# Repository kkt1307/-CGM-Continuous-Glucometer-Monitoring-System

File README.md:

# Indigenous Continuous Glucose Monitoring (CGM) System

**Electrochemical Sensor Interface | Custom Analog Front End | PCB Design | ESP32 | IoT**

## Overview

This project focuses on the development of an indigenous Continuous Glucose Monitoring (CGM) prototype using an electrochemical sensing interface, a custom Analog Front End (AFE), and an ESP32-based embedded acquisition system.

The work involved studying and reverse-engineering a commercial CGM sensor interface, developing custom signal-conditioning circuitry, designing PCBs, acquiring low-level electrochemical sensor signals, and implementing remote data logging using Firebase.

The primary engineering focus was on analog signal acquisition, sensor interfacing, hardware development, and embedded data processing.

## System Architecture

The system follows this signal acquisition pipeline:

1. Electrochemical glucose sensor
2. Custom potentiostat and Transimpedance Amplifier (TIA)
3. Analog-to-Digital Conversion
4. ESP32-based data acquisition
5. Python communication bridge
6. Firebase Realtime Database

## Technical Contributions

### 1. Electrochemical Sensor Interface
- Studied the working principle of electrochemical glucose sensors.
- Investigated the three-electrode sensing architecture: Working Electrode (WE), Reference Electrode (RE), and Counter Electrode (CE).
- Reverse-engineered the interface of a commercial CGM sensor.
- Investigated sensor current characteristics and electrical response.

### 2. Custom Analog Front End (AFE)
- Designed a custom analog front end for electrochemical signal acquisition.
- Developed Transimpedance Amplifier (TIA) circuits for converting low-level sensor currents into measurable voltages.
- Worked on virtual ground generation and precision voltage referencing.
- Investigated gain selection, signal conditioning, and analog stability.
- Simulated circuit behavior using LTSpice.

### 3. PCB Design and Hardware Development
- Designed circuit schematics and PCB layouts using KiCad.
- Integrated analog signal-conditioning stages, ADC interfacing, voltage regulation, and sensor connectors.
- Worked on grounding, power distribution, and analog signal routing.
- Prepared BOMs and Gerber manufacturing files.
- Evaluated PCB fabrication and assembly requirements.

### 4. Embedded Systems and Data Acquisition
- Developed ESP32 firmware for sensor data acquisition.
- Implemented ADC sampling and voltage conversion.
- Processed sensor measurements using filtering techniques.
- Calculated sensor current from the measured TIA output and feedback resistance.
- Implemented serial communication for transferring measurement data.

### 5. IoT and Remote Data Monitoring
- Developed a Python-based communication bridge.
- Integrated sensor measurements with Firebase Realtime Database.
- Implemented real-time logging of ADC values, TIA voltage, sensor current, and device status.

## Hardware Components

| Component | Application |
|---|---|
| ESP32 | Embedded controller |
| Operational Amplifiers | Custom analog front end |
| ADS1115 | External ADC |
| LM4040 | Precision voltage reference |
| AP2112K-3.3 | Voltage regulation |
| TVS / ESD Protection | Circuit protection |
| Electrochemical Sensor | Glucose sensing interface |

*Component selection may vary across prototype revisions.*

## Software and Tools

- **PCB Design:** KiCad
- **Circuit Simulation:** LTSpice
- **Embedded Development:** Arduino IDE, C/C++
- **Microcontroller:** ESP32
- **Data Processing:** Python
- **Database:** Firebase Realtime Database
- **Communication:** Serial Communication

## Experimental Results

The prototype was tested for electrical signal acquisition and sensor-current measurement.

Example measurements:

| ADC Reading | TIA Output | Sensor Current |
|---:|---:|---:|
| 111 | 89.45 mV | 4.47 µA |
| 251 | 202.27 mV | 10.11 µA |

The measurements demonstrate the acquisition and conversion of low-level sensor currents into digital readings.

Additional characterization data and measurement plots are available in the `results/` directory.

## Repository Structure

```text
├── docs/          # Project documentation
├── hardware/      # Schematics, PCB layouts and BOM
├── firmware/      # ESP32 firmware
├── software/      # Python and Firebase integration
├── simulation/    # LTSpice simulations
├── results/       # Experimental data and plots
└── images/        # Prototype and PCB photographs
```

## Current Development Status

The project covers prototype-level electronics development, analog signal acquisition, embedded firmware, and remote data logging.

Further work is required for:
- Sensor-specific glucose calibration.
- Long-term sensor stability and drift characterization.
- Temperature compensation.
- Measurement accuracy and repeatability evaluation.
- Clinical validation and safety evaluation.

**Note:** This is an electronics development prototype and is not a clinically validated glucose monitoring device. Its readings should not be used for medical decisions.

## Acknowledgements

Developed as part of research and hardware development work at the Centre for Nanotechnology, IIT Guwahati.

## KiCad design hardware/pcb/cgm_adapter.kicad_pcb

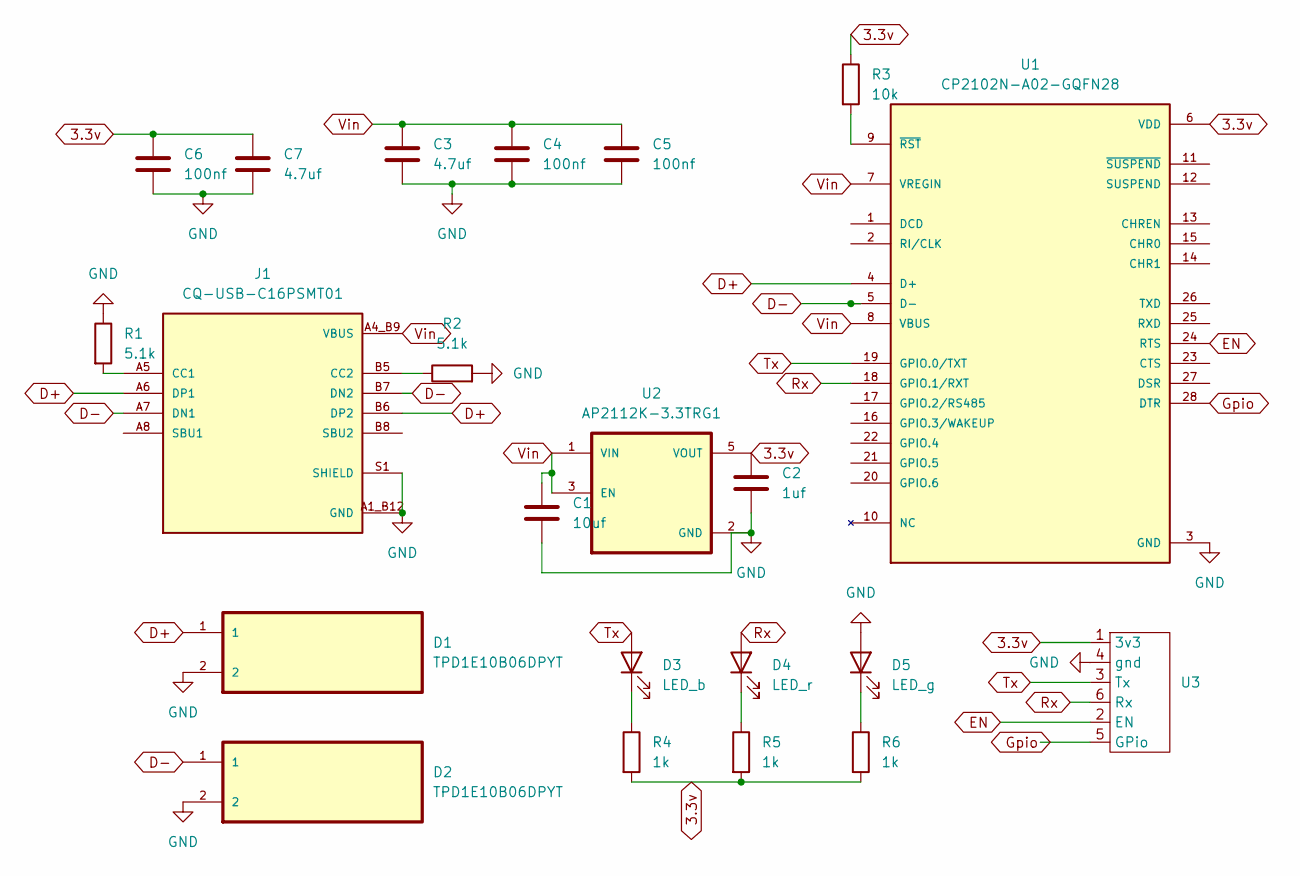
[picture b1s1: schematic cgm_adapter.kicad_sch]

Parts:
C1: 10uf; C_0201_0603Metric
C2: 1uf; C_0201_0603Metric
C3, C7: 4.7uf; C_0201_0603Metric
C4, C5, C6: 100nf; C_0201_0603Metric
D1, D2: TPD1E10B06DPYT; DIO_TPD1E05U06DPYR
D3: LED_b; LED_0603_1608Metric
D4: LED_r; LED_0603_1608Metric
D5: LED_g; LED_0603_1608Metric
J1: CQ-USB-C16PSMT01; SHENZHEN-CHUANGQIN-TECHNOLOGY_CQ-USB-C16PSMT01; PARTREV A
R1, R2: 5.1k; R_0201_0603Metric
R3: 10k; R_0201_0603Metric
R4, R5, R6: 1k; R_0201_0603Metric
U1: CP2102N-A02-GQFN28; QFN50P500X500X80-29N; PARTREV 1.5
U2: AP2112K-3.3TRG1; SOT95P285X140-5N; PARTREV 2-2
U3: 3x2_pogo_pins

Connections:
3.3v: C2.1, C6.1, C7.1, R3.1, R4.2, R5.2, R6.2, U1.6 (VDD), U2.5 (VOUT), U3.1 (3v3)
D+: D1.1, J1.A6 (DP1), J1.B6 (DP2), U1.4 (D+)
D-: D2.1, J1.A7 (DN1), J1.B7 (DN2), U1.5 (D-)
EN: U1.24 (RTS), U3.2 (EN)
GND: C1.2, C2.2, C3.2, C4.2, C5.2, C6.2, C7.2, D1.2, D2.2, D5.2 (A), J1.A1_B12 (GND), J1.B1_A12 (GND), J1.S1 (SHIELD), J1.S2 (SHIELD), J1.S3 (SHIELD), J1.S4 (SHIELD), R1.1, R2.2, U1.3 (GND), U1.29 (GND), U2.2 (GND), U3.4 (gnd)
Gpio: U1.28 (DTR), U3.5 (GPio)
unnamed: D3.1 (K), R4.1
unnamed: D4.1 (K), R5.1
unnamed: D5.1 (K), R6.1
unnamed: J1.A5 (CC1), R1.2
unnamed: J1.B5 (CC2), R2.1
unnamed: R3.2, U1.9 (~RST)
Rx: D4.2 (A), U1.18 (GPIO.1/RXT), U3.6 (Rx)
Tx: D3.2 (A), U1.19 (GPIO.0/TXT), U3.3 (Tx)
Vin: C1.1, C3.1, C4.1, C5.1, J1.A4_B9 (VBUS), J1.B4_A9 (VBUS), U1.7 (VREGIN), U1.8 (VBUS), U2.1 (VIN), U2.3 (EN)

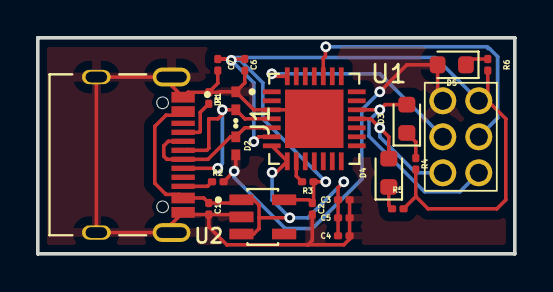
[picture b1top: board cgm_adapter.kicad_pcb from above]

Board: 2 copper layers, 26.5 x 12.0 mm, 22 parts (0 on the bottom side), 15 nets.

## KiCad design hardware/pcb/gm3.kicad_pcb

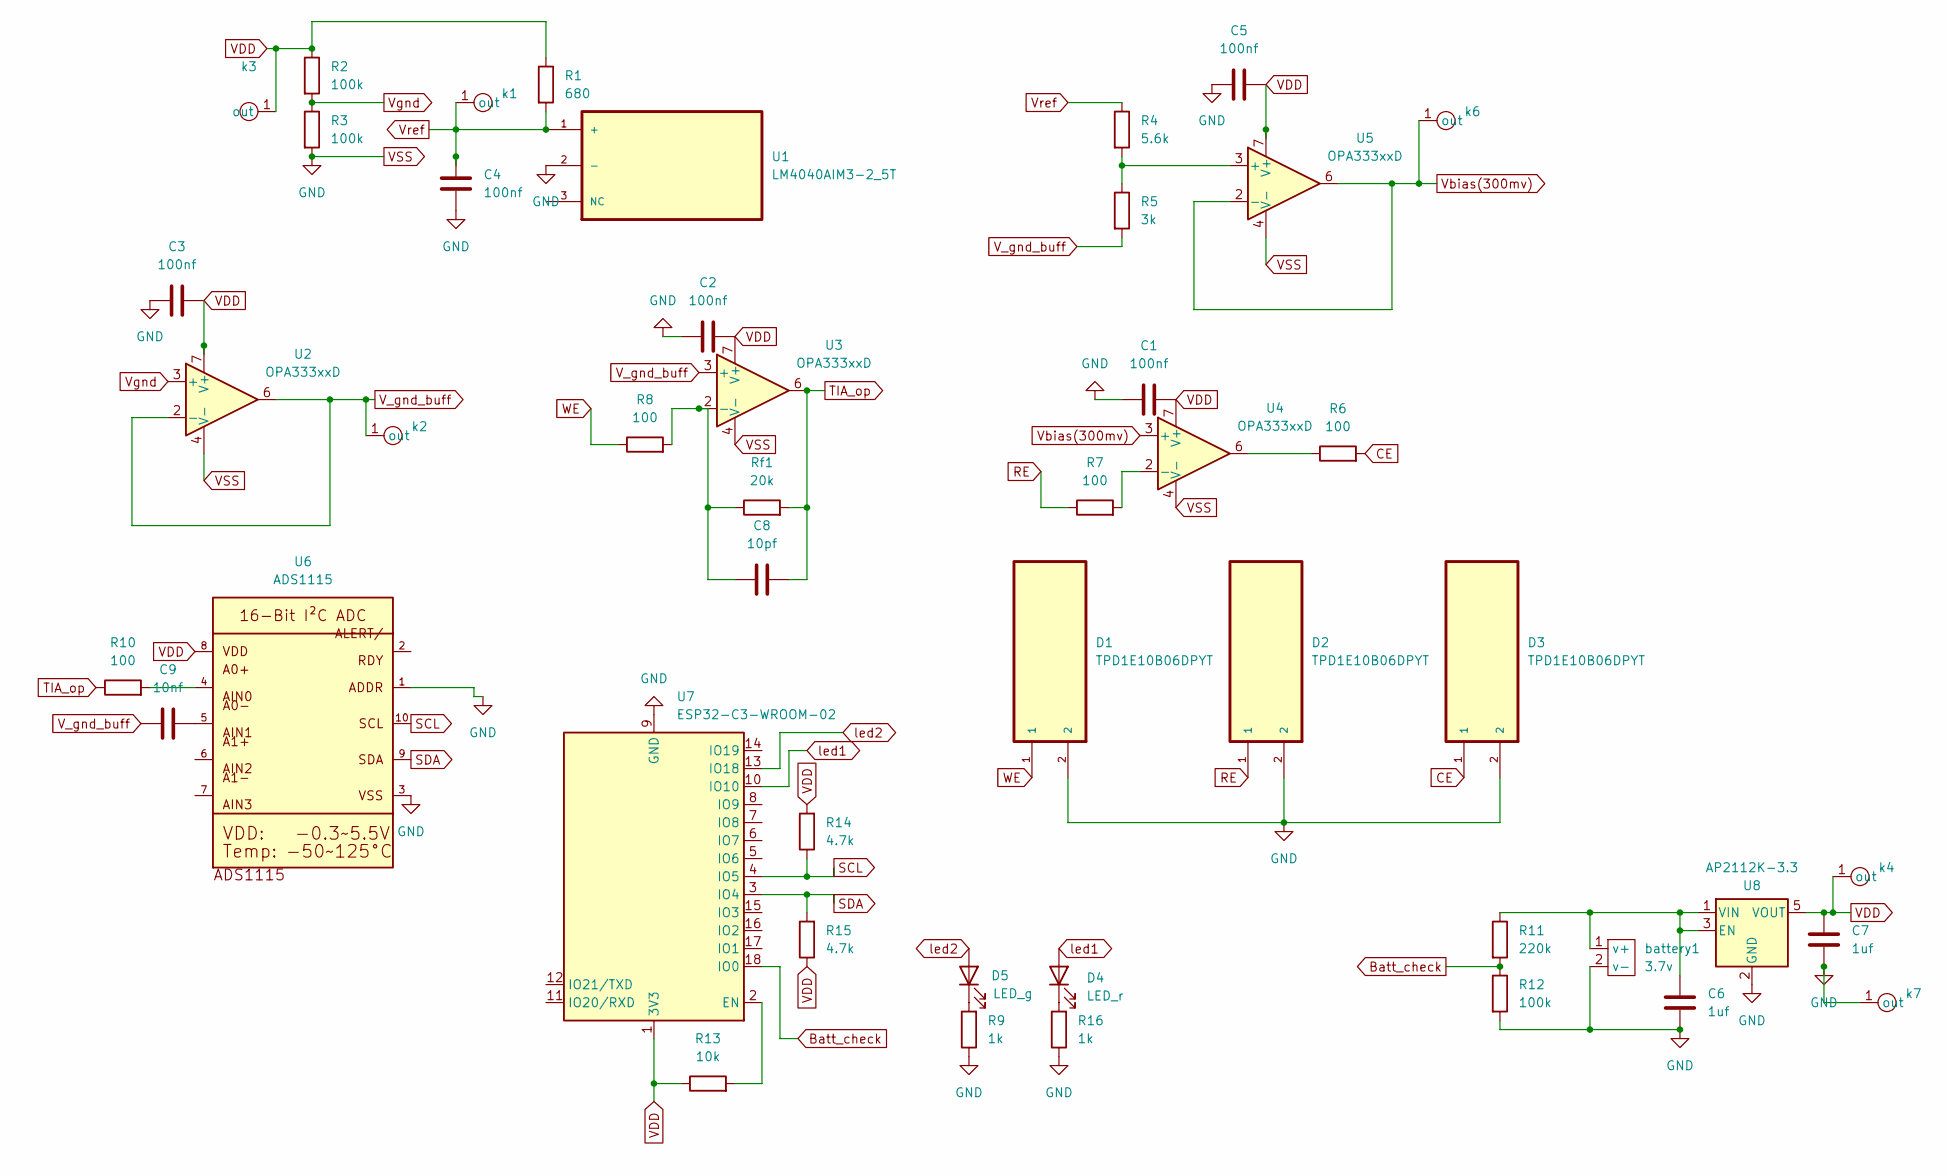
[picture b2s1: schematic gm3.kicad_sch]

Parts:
C1, C2, C3, C4, C5: 100nf; C_0201_0603Metric
C6, C7: 1uf; C_0201_0603Metric
C8: 10pf; C_0201_0603Metric
C9: 10nf; C_0201_0603Metric
D1, D2, D3: TPD1E10B06DPYT; DIO_TPD1E05U06DPYR
D4: LED_r; LED_0603_1608Metric
D5: LED_g; LED_0603_1608Metric
R1: 680; R_0201_0603Metric
R2, R3, R12: 100k; R_0201_0603Metric
R4: 5.6k; R_0201_0603Metric
R5: 3k; R_0201_0603Metric
R6, R7, R8, R10: 100; R_0201_0603Metric
R9, R16: 1k; R_0201_0603Metric
R11: 220k; R_0201_0603Metric
R13: 10k; R_0201_0603Metric
R14, R15: 4.7k; R_0201_0603Metric
Rf1: 20k; R_0201_0603Metric
U1: LM4040AIM3-2_5T; SOT95P237X112-3N
U2, U3, U4, U5: OPA333xxD; SOIC-8_3.9x4.9mm_P1.27mm
U6: ADS1115; MSOP10
U7: ESP32-C3-WROOM-02
U8: AP2112K-3.3; SOT-23-5
battery1: 3.7v; batt_pad
k1, k2, k3, k4, k6, k7: chech_pad

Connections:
Batt_check: R11.2, R12.1, U7.18 (IO0)
CE: D3.1, R6.2
unnamed: C9.2, U6.5
unnamed: D4.1 (K), R16.2
unnamed: D5.1 (K), R9.2
unnamed: R6.1, U4.6
unnamed: R10.2, U6.4
unnamed: C8.1, R8.2, Rf1.1, U3.2 (-)
unnamed: R7.2, U4.2 (-)
unnamed: R4.2, R5.1, U5.3 (+)
unnamed: R13.2, U7.2 (EN)
unnamed: C6.1, R11.1, U8.1 (VIN), U8.3 (EN), battery1.1 (v+)
RE: D2.1, R7.1
SCL: R14.1, U6.10, U7.4 (IO5)
SDA: R15.2, U6.9, U7.3 (IO4)
TIA_op: C8.2, R10.1, Rf1.2, U3.6
VDD: C1.2, C2.2, C3.1, C5.2, C7.1, R1.1, R2.1, R13.1, R14.2, R15.1, U2.7 (V+), U3.7 (V+), U4.7 (V+), U5.7 (V+), U6.8, U7.1 (3V3), U8.5 (VOUT), k3.1, k4.1 (out)
VSS: C1.1, C2.1, C3.2, C4.1, C5.1, C6.2, C7.2, D1.2, D2.2, D3.2, R3.2, R9.1, R12.2, R16.1, U1.2 (-), U2.4 (V-), U3.4 (V-), U4.4 (V-), U5.4 (V-), U6.1, U6.3, U7.9 (GND), U7.19 (GND), U8.2 (GND), battery1.2 (v-), k7.1 (out)
V_gnd_buff: C9.1, R5.2, U2.2 (-), U2.6, U3.3 (+), k2.1 (out)
Vbias(300mv): U4.3 (+), U5.2 (-), U5.6, k6.1 (out)
Vgnd: R2.2, R3.1, U2.3 (+)
Vref: C4.2, R1.2, R4.1, U1.1 (+), k1.1 (out)
WE: D1.1, R8.1
led1: D4.2 (A), U7.10 (IO10)
led2: D5.2 (A), U7.13 (IO18)

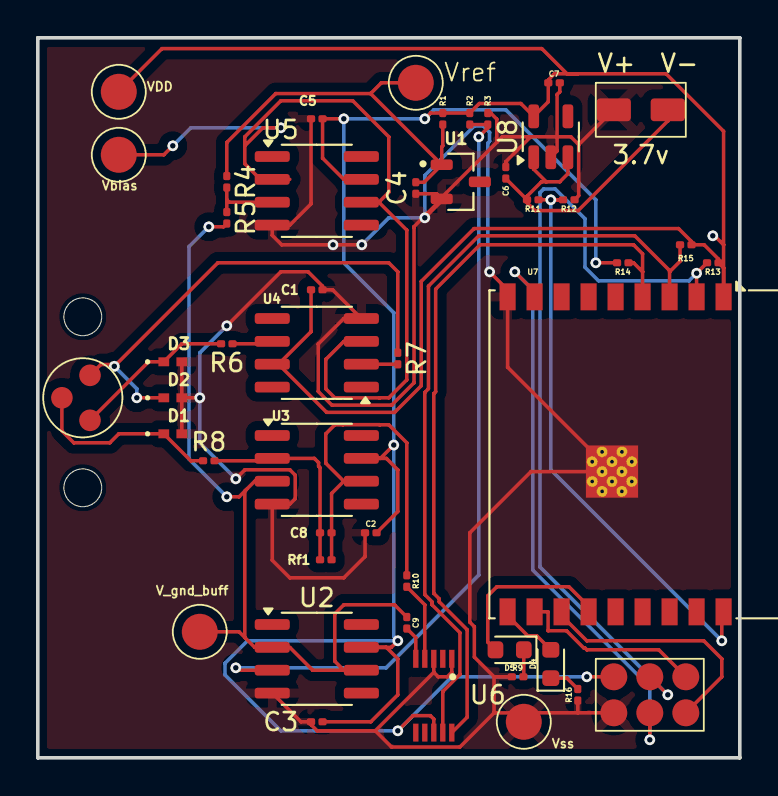
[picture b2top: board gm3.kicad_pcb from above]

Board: 2 copper layers, 39.0 x 40.0 mm, 45 parts (0 on the bottom side), 25 nets.

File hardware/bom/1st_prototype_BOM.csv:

"Reference","Qty","Value","DNP","Exclude from BOM","Exclude from Board","Footprint","Datasheet"
"battery1","1","3.7v","","","","my_lib:batt_pad",""
"C1,C2,C3,C4,C5","5","100nf","","","","Capacitor_SMD:C_0201_0603Metric","~"
"C6,C7","2","1uf","","","","Capacitor_SMD:C_0201_0603Metric","~"
"C8","1","10pf","","","","Capacitor_SMD:C_0201_0603Metric","~"
"C9","1","10nf","","","","Capacitor_SMD:C_0201_0603Metric","~"
"D1,D2,D3","3","TPD1E10B06DPYT","","","","TPD1E10B06DPYT:DIO_TPD1E05U06DPYR",""
"D4","1","LED_r","","","","LED_SMD:LED_0603_1608Metric","~"
"D5","1","LED_g","","","","LED_SMD:LED_0603_1608Metric","~"
"k1,k2,k3,k4,k6,k7","6","~","","","","my_lib:chech_pad",""
"R1","1","680","","","","Resistor_SMD:R_0201_0603Metric","~"
"R2,R3,R12","3","100k","","","","Resistor_SMD:R_0201_0603Metric","~"
"R4","1","5.6k","","","","Resistor_SMD:R_0201_0603Metric","~"
"R5","1","3k","","","","Resistor_SMD:R_0201_0603Metric","~"
"R6,R7,R8,R10","4","100","","","","Resistor_SMD:R_0201_0603Metric","~"
"R9,R16","2","1k","","","","Resistor_SMD:R_0201_0603Metric","~"
"R11","1","220k","","","","Resistor_SMD:R_0201_0603Metric","~"
"R13,Rf1","2","10k","","","","Resistor_SMD:R_0201_0603Metric","~"
"R14,R15","2","4.7k","","","","Resistor_SMD:R_0201_0603Metric","~"
"U1","1","LM4040AIM3-2_5T","","","","LM4040AIM3-2_5T:SOT95P237X112-3N",""
"U2,U3,U4,U5","4","OPA333xxD","","","","Package_SO:SOIC-8_3.9x4.9mm_P1.27mm","http://www.ti.com/lit/ds/symlink/opa333.pdf"
"U6","1","ADS1115","","","","ADS1115:MSOP10",""
"U7","1","ESP32-C3-WROOM-02","","","","RF_Module:ESP32-C3-WROOM-02","https://www.espressif.com/sites/default/files/documentation/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"
"U8","1","AP2112K-3.3","","","","Package_TO_SOT_SMD:SOT-23-5","https://www.diodes.com/assets/Datasheets/AP2112.pdf"
